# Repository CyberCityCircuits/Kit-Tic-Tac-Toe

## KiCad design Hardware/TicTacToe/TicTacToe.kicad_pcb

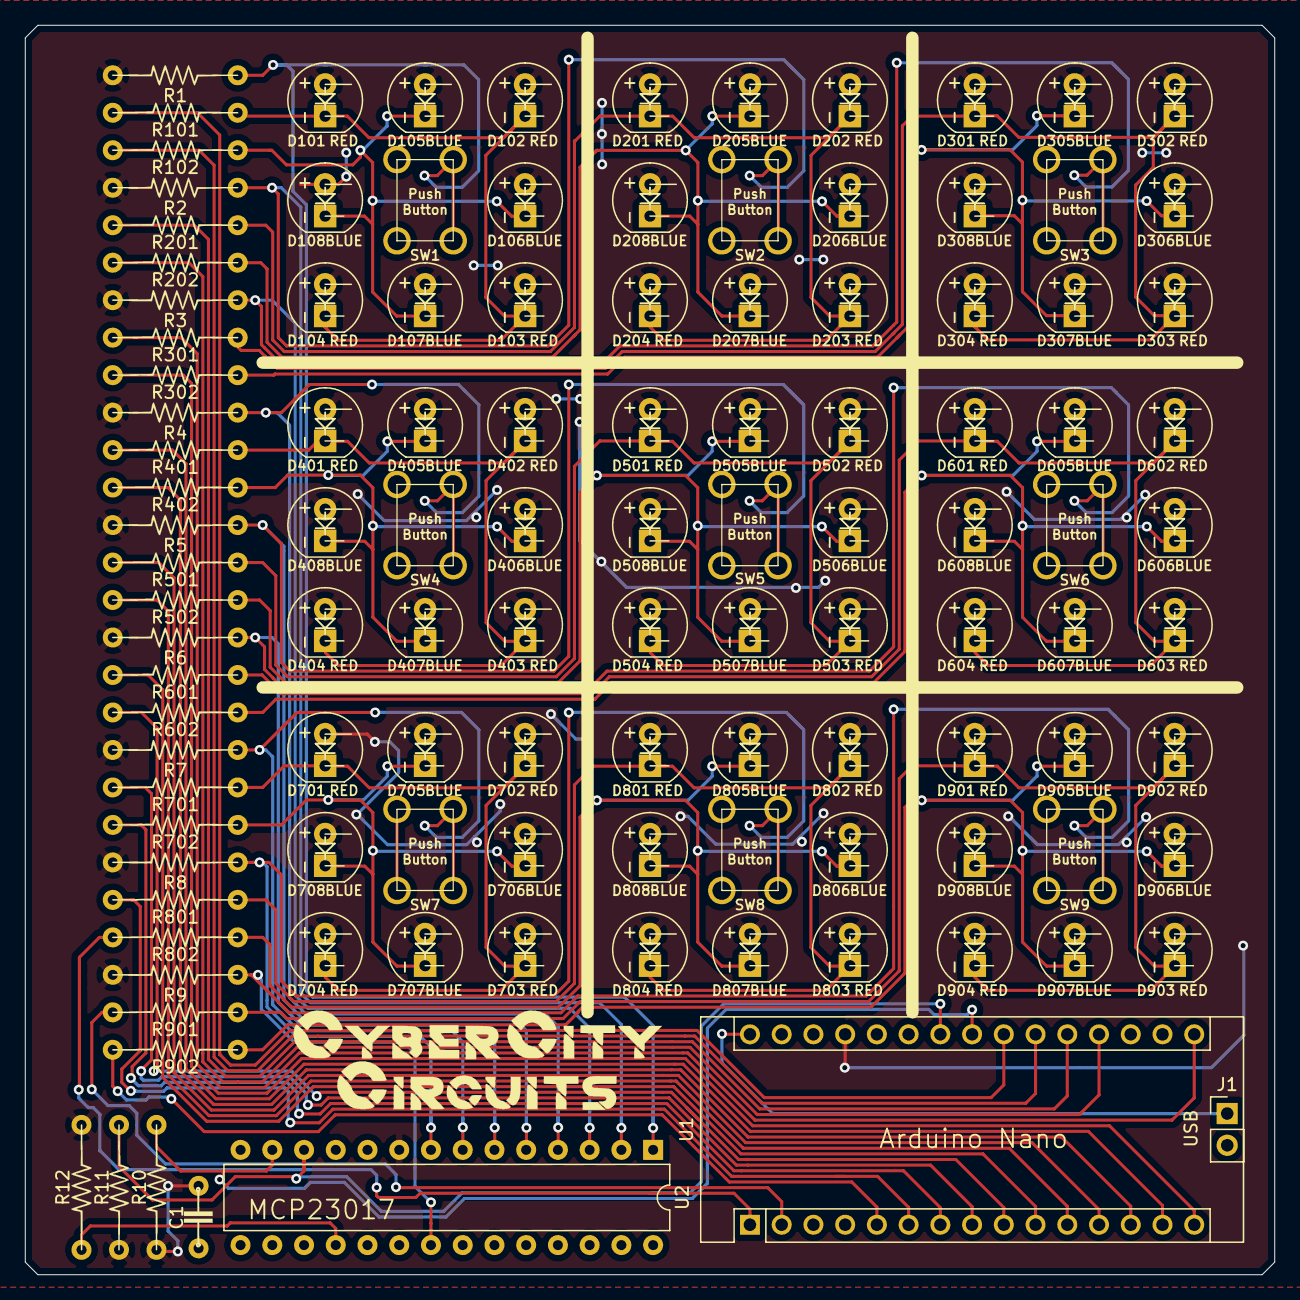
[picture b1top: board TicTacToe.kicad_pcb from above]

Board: 2 copper layers, 100.0 x 100.0 mm, 115 parts (0 on the bottom side), 51 nets.

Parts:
C1: 0.1uF; Schematic - Capacitor 5.0mm
D101, D102, D103, D104, D201, D202, D203, D204, D301, D302, D303, D304, D401, D402, D403, D404, D501, D502, D503, D504, D601, D602, D603, D604, D701, D702, D703, D704, D801, D802, D803, D804, D901, D902, D903, D904: RED; Schematic_-_LED_5mm(2.56P)_004
D105, D106, D107, D108, D205, D206, D207, D208, D305, D306, D307, D308, D405, D406, D407, D408, D505, D506, D507, D508, D605, D606, D607, D608, D705, D706, D707, D708, D805, D806, D807, D808, D905, D906, D907, D908: BLUE; Schematic_-_LED_5mm(2.56P)_004
J1: Screw_Terminal_01x02; PinHeader_1x02_P2.54mm_Vertical
R1, R2, R3, R4, R5, R6, R7, R8, R9, R12: 10K; Schematic - Resistor 10.00mm
R10, R11: 4.7K; Schematic - Resistor 10.00mm
R101, R102, R201, R202, R301, R302, R401, R402, R501, R502, R601, R602, R701, R702, R801, R802, R901, R902: 470; Schematic - Resistor 10.00mm
SW1, SW2, SW3, SW4, SW5, SW6, SW7, SW8, SW9: SW_Push; Schematic_-_Button_Labeled
U1: Arduino_Nano_Every; Arduino_Nano
U2: MCP23017_SP; DIP-28_W7.62mm

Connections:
5V: C1.2, D101.2, D102.2, D103.2, D104.2, D105.2, D106.2, D107.2, D108.2, D201.2, D202.2, D203.2, D204.2, D205.2, D206.2, D207.2, D208.2, D301.2, D302.2, D303.2, D304.2, D305.2, D306.2, D307.2, D308.2, D401.2, D402.2, D403.2, D404.2, D405.2, D406.2, D407.2, D408.2, D501.2, D502.2, D503.2, D504.2, D505.2, D506.2, D507.2, D508.2, D601.2, D602.2, D603.2, D604.2, D605.2, D606.2, D607.2, D608.2, D701.2, D702.2, D703.2, D704.2, D705.2, D706.2, D707.2, D708.2, D801.2, D802.2, D803.2, D804.2, D805.2, D806.2, D807.2, D808.2, D901.2, D902.2, D903.2, D904.2, D905.2, D906.2, D907.2, D908.2, R1.1, R2.1, R3.1, R4.1, R5.1, R6.1, R7.1, R8.1, R9.1, R10.1, R11.1, R12.2, U1.27, U2.9
BATT: J1.1, U1.30
BUTTON_1: R1.2, SW1.2, U2.1
BUTTON_2: R2.2, SW2.2, U2.2
BUTTON_3: R3.2, SW3.2, U2.3
BUTTON_4: R4.2, SW4.2, U2.4
BUTTON_5: R5.2, SW5.2, U2.5
BUTTON_6: R6.2, SW6.2, U2.6
BUTTON_7: R7.2, SW7.2, U2.7
BUTTON_8: R8.2, SW8.2, U2.8
BUTTON_9: R9.2, SW9.2, U2.21
D00_RX: R901.2, U1.2
D01_TX: R802.2, U1.1
D02: R902.2, U1.5
D03: R801.2, U1.6
D04: R702.2, U1.7
D05: R701.2, U1.8
D06: R602.2, U1.9
D07: R601.2, U1.10
D08: R502.2, U1.11
D09: R501.2, U1.12
D10: R402.2, U1.13
D11: R401.2, U1.14
D12: R302.2, U1.15
D13: R301.2, U1.16
D14: R202.2, U1.19
D15: R201.2, U1.20
D16: R102.2, U1.21
D17: R101.2, U1.22
GND: C1.1, J1.2, SW1.1, SW2.1, SW3.1, SW4.1, SW5.1, SW6.1, SW7.1, SW8.1, SW9.1, U1.4, U1.29, U2.10, U2.15, U2.16, U2.17
unnamed: D101.1, D102.1, D103.1, D104.1, R101.1
unnamed: D105.1, D106.1, D107.1, D108.1, R102.1
unnamed: D201.1, D202.1, D203.1, D204.1, R201.1
unnamed: D205.1, D206.1, D207.1, D208.1, R202.1
unnamed: D301.1, D302.1, D303.1, D304.1, R301.1
unnamed: D305.1, D306.1, D307.1, D308.1, R302.1
unnamed: D401.1, D402.1, D403.1, D404.1, R401.1
unnamed: D405.1, D406.1, D407.1, D408.1, R402.1
unnamed: D501.1, D502.1, D503.1, D504.1, R501.1
unnamed: D505.1, D506.1, D507.1, D508.1, R502.1
unnamed: D601.1, D602.1, D603.1, D604.1, R601.1
unnamed: D605.1, D606.1, D607.1, D608.1, R602.1
unnamed: D701.1, D702.1, D703.1, D704.1, R701.1
unnamed: D705.1, D706.1, D707.1, D708.1, R702.1
unnamed: D801.1, D802.1, D803.1, D804.1, R801.1
unnamed: D805.1, D806.1, D807.1, D808.1, R802.1
unnamed: D901.1, D902.1, D903.1, D904.1, R901.1
unnamed: D905.1, D906.1, D907.1, D908.1, R902.1
unnamed: R12.1, U2.18
SCL: R11.2, U1.24, U2.12
SDA: R10.2, U1.23, U2.13

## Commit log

2021-04-27 April 2021 Cyber Box
